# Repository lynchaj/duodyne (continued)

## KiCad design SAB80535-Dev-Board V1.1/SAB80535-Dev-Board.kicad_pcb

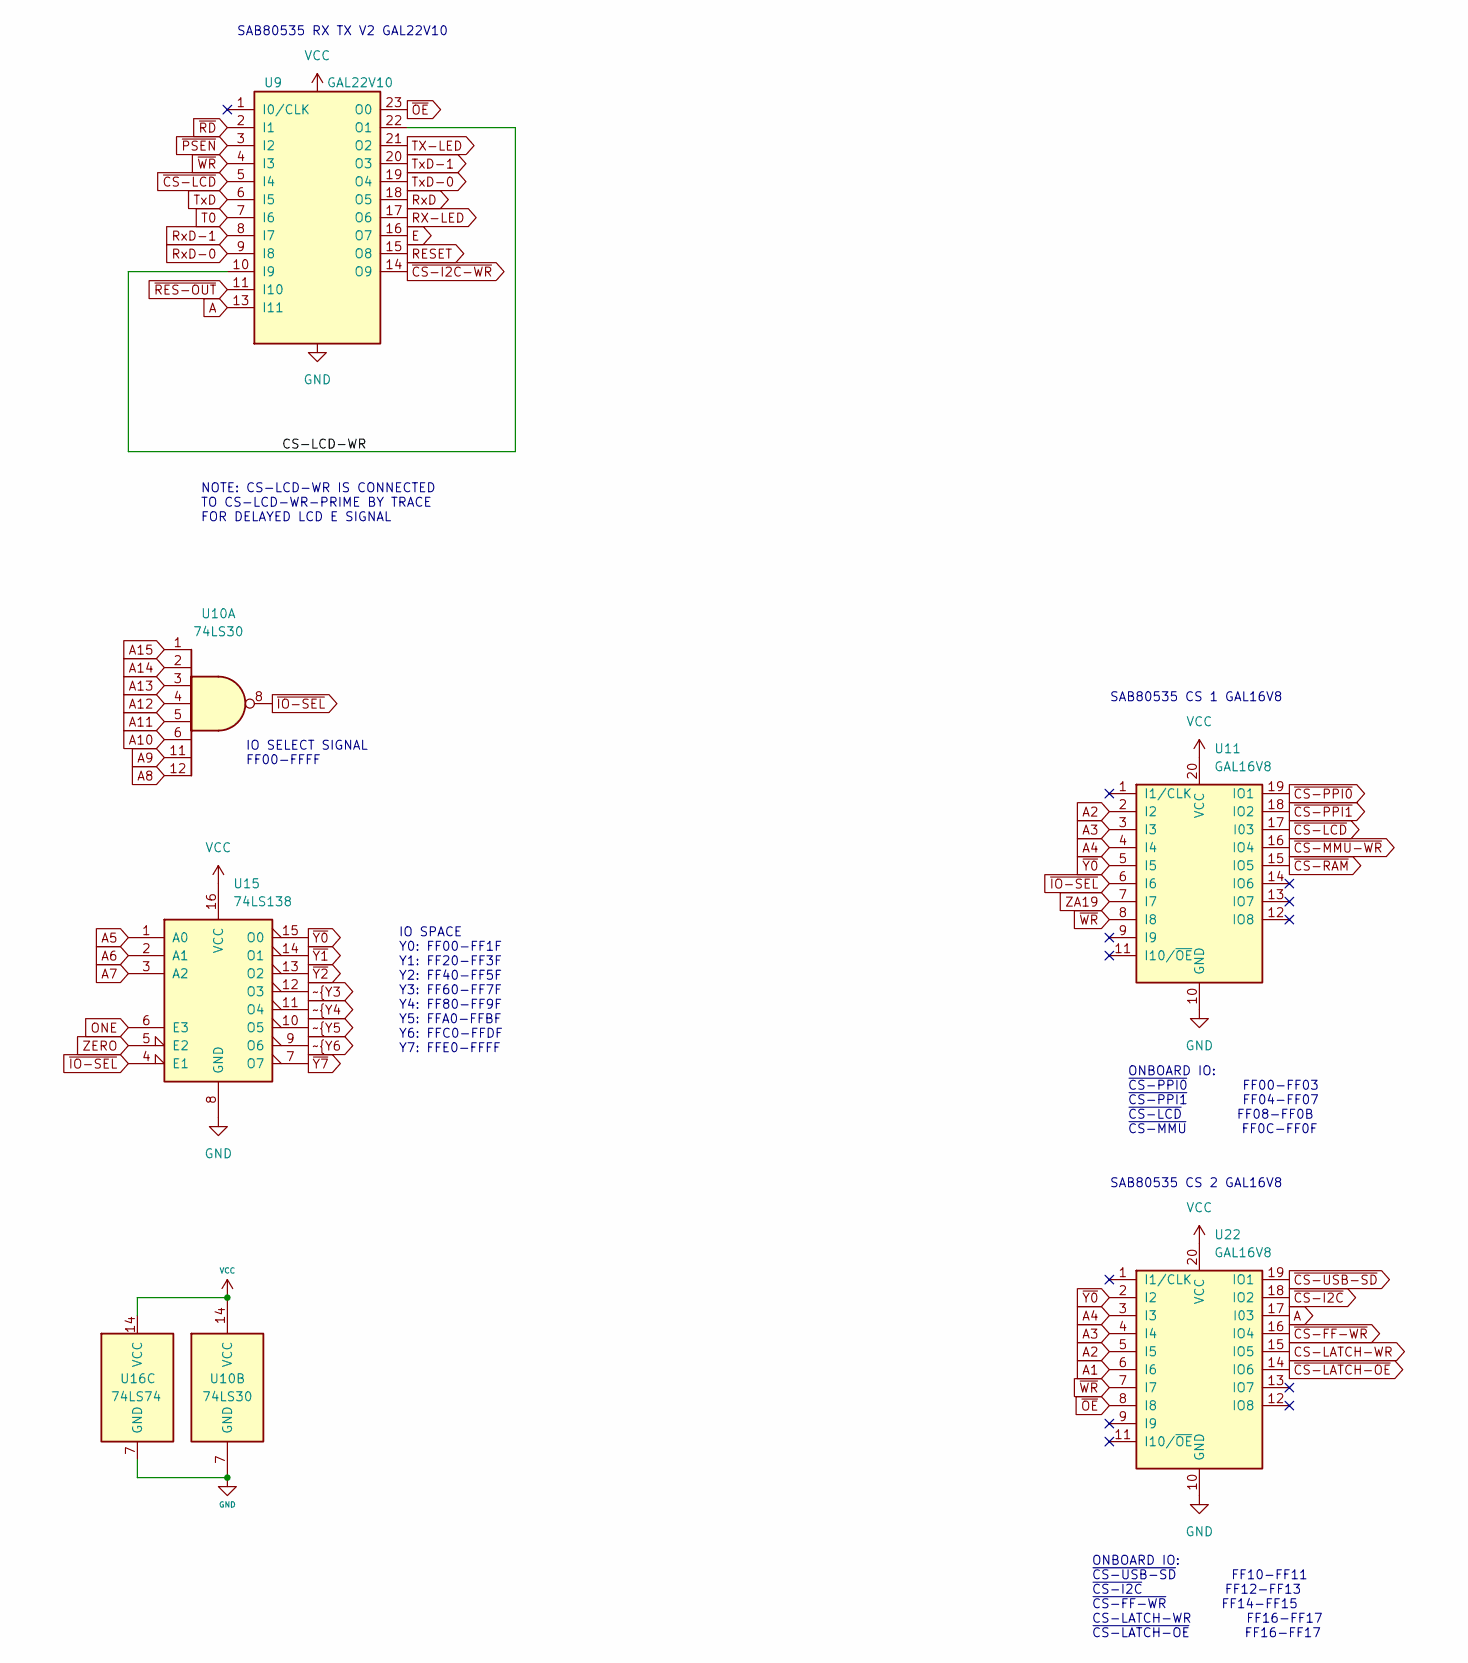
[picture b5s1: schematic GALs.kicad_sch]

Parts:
U9: GAL22V10; DIP-24_W7.62mm_Socket
U10: 74LS30; DIP-14_W7.62mm_Socket
U11, U22: GAL16V8; DIP-20_W7.62mm_Socket
U15: 74LS138; DIP-16_W7.62mm_Socket
U16: 74LS74; DIP-14_W7.62mm_Socket

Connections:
/GALs/CS-LCD-WR: U9.10 (I9), U9.22 (O1)
A: U9.13 (I11), U22.17 (I03)
A1: U22.6 (I6); also elsewhere on the board
A2: U11.2 (I2), U22.5 (I5); also elsewhere on the board
A3: U11.3 (I3), U22.4 (I4); also elsewhere on the board
A4: U11.4 (I4), U22.3 (I3); also elsewhere on the board
A5: U15.1 (A0); also elsewhere on the board
A6: U15.2 (A1); also elsewhere on the board
A7: U15.3 (A2); also elsewhere on the board
A8: U10.12; also elsewhere on the board
A9: U10.11; also elsewhere on the board
A10: U10.6; also elsewhere on the board
A11: U10.5; also elsewhere on the board
A12: U10.4; also elsewhere on the board
A13: U10.3; also elsewhere on the board
A14: U10.2; also elsewhere on the board
A15: U10.1; also elsewhere on the board
CS-LATCH-WR: U22.15 (IO5); also elsewhere on the board
D0: U16.2 (D); also elsewhere on the board
E: U9.16 (O7); also elsewhere on the board
GND: U9.12 (GND), U10.7 (GND), U11.10 (GND), U15.8 (GND), U16.7 (GND), U22.10 (GND); also elsewhere on the board
ONE: U15.6 (E3), U16.4 (~S); also elsewhere on the board
RESET: U9.15 (O8); also elsewhere on the board
RX-LED: U9.17 (O6); also elsewhere on the board
RxD: U9.18 (O5); also elsewhere on the board
RxD-0: U9.9 (I8); also elsewhere on the board
RxD-1: U9.8 (I7); also elsewhere on the board
T0: U9.7 (I6); also elsewhere on the board
TX-LED: U9.21 (O2); also elsewhere on the board
TxD: U9.6 (I5); also elsewhere on the board
TxD-0: U9.19 (O4); also elsewhere on the board
TxD-1: U9.20 (O3); also elsewhere on the board
VCC: U9.24 (VCC), U10.14 (VCC), U11.20 (VCC), U15.16 (VCC), U16.14 (VCC), U22.20 (VCC); also elsewhere on the board
ZA19: U11.7 (I7); also elsewhere on the board
ZERO: U15.5 (E2); also elsewhere on the board
~CS-FF-WR: U16.3 (C), U22.16 (IO4); also elsewhere on the board
~CS-I2C-WR: U9.14 (O9); also elsewhere on the board
~CS-I2C: U22.18 (IO2); also elsewhere on the board
~CS-LATCH-OE: U22.14 (IO6); also elsewhere on the board
~CS-LCD: U9.5 (I4), U11.17 (I03); also elsewhere on the board
~CS-MMU-WR: U11.16 (IO4); also elsewhere on the board
~CS-PPI0: U11.19 (IO1); also elsewhere on the board
~CS-PPI1: U11.18 (IO2); also elsewhere on the board
~CS-RAM: U11.15 (IO5); also elsewhere on the board
~CS-ROM: U11.14 (IO6); also elsewhere on the board
~CS-USB-SD: U22.19 (IO1); also elsewhere on the board
~IO-SEL: U10.8, U11.6 (I6), U15.4 (E1); also elsewhere on the board
~OE: U9.23 (O0), U22.8 (I8); also elsewhere on the board
~PAGE-EN: U16.6 (~Q); also elsewhere on the board
~PSEN: U9.3 (I2); also elsewhere on the board
~RD: U9.2 (I1); also elsewhere on the board
~RES-OUT: U9.11 (I10), U16.1 (~R); also elsewhere on the board
~WR: U9.4 (I3), U11.8 (I8), U22.7 (I7); also elsewhere on the board
~Y0: U11.5 (I5), U15.15 (O0), U22.2 (I2)
~Y1: U15.14 (O1); also elsewhere on the board
~Y2: U15.13 (O2); also elsewhere on the board
~Y7: U15.7 (O7); also elsewhere on the board

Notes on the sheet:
NOTE: CS-LCD-WR IS CONNECTED TO CS-LCD-WR-PRIME BY TRACE FOR DELAYED LCD E SIGNAL
SAB80535 RX TX V2 GAL22V10
IO SELECT SIGNAL FF00-FFFF
SAB80535 CS 2 GAL16V8
IO SPACE Y0: FF00-FF1F Y1: FF20-FF3F Y2: FF40-FF5F Y3: FF60-FF7F Y4: FF80-FF9F Y5: FFA0-FFBF Y6: FFC0-FFDF Y7: FFE0-FFFF
ONBOARD IO: ~{CS-USB-SD} FF10-FF11 ~{CS-I2C} FF12-FF13 ~{CS-FF-WR} FF14-FF15 CS-LATCH-WR FF16-FF17 ~{CS-LATCH-OE} FF16-FF17
SAB80535 CS 1 GAL16V8
ONBOARD IO: ~{CS-PPI0} FF00-FF03 ~{CS-PPI1} FF04-FF07 ~{CS-LCD} FF08-FF0B ~{CS-MMU} FF0C-FF0F

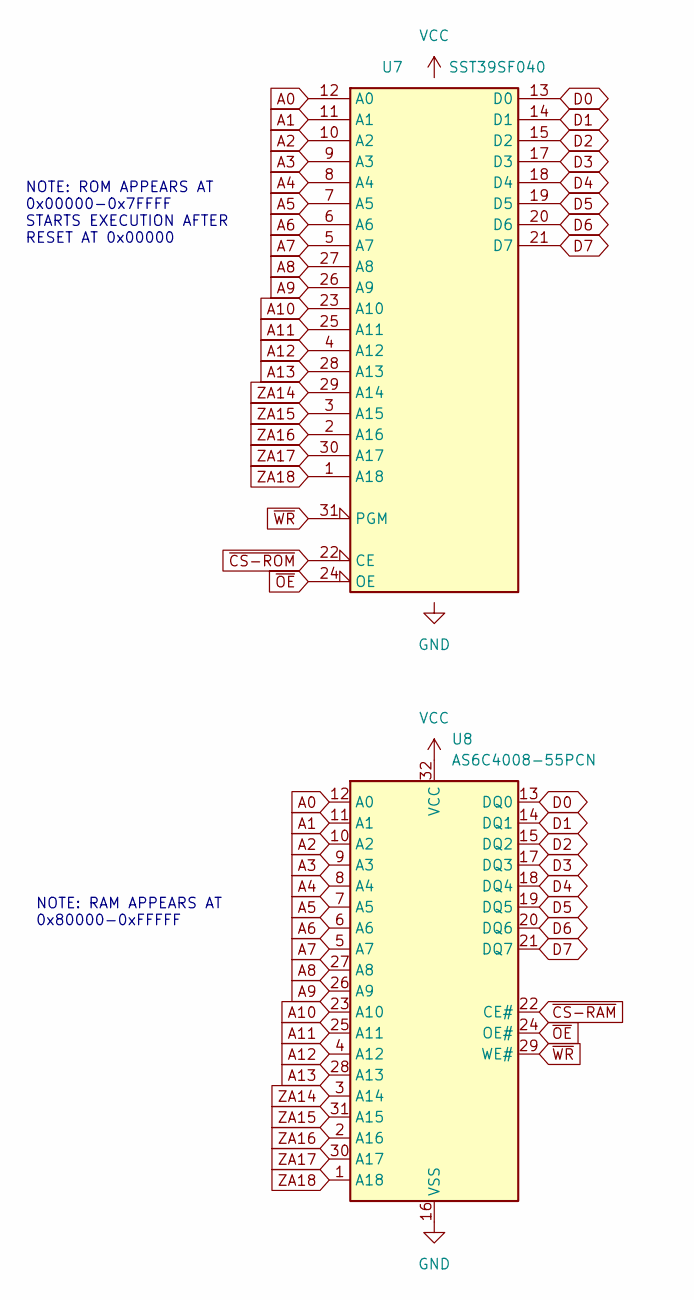
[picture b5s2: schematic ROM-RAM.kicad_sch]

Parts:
U7: SST39SF040; DIP_Socket-32_W11.9_W12.7_W15.24_W17.78_W18.5_3M_232-1285-0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
U8: AS6C4008-55PCN; DIP-32_W15.24mm_Socket

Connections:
A0: U7.12 (A0), U8.12 (A0); also elsewhere on the board
A1: U7.11 (A1), U8.11 (A1); also elsewhere on the board
A2: U7.10 (A2), U8.10 (A2); also elsewhere on the board
A3: U7.9 (A3), U8.9 (A3); also elsewhere on the board
A4: U7.8 (A4), U8.8 (A4); also elsewhere on the board
A5: U7.7 (A5), U8.7 (A5); also elsewhere on the board
A6: U7.6 (A6), U8.6 (A6); also elsewhere on the board
A7: U7.5 (A7), U8.5 (A7); also elsewhere on the board
A8: U7.27 (A8), U8.27 (A8); also elsewhere on the board
A9: U7.26 (A9), U8.26 (A9); also elsewhere on the board
A10: U7.23 (A10), U8.23 (A10); also elsewhere on the board
A11: U7.25 (A11), U8.25 (A11); also elsewhere on the board
A12: U7.4 (A12), U8.4 (A12); also elsewhere on the board
A13: U7.28 (A13), U8.28 (A13); also elsewhere on the board
D0: U7.13 (D0), U8.13 (DQ0); also elsewhere on the board
D1: U7.14 (D1), U8.14 (DQ1); also elsewhere on the board
D2: U7.15 (D2), U8.15 (DQ2); also elsewhere on the board
D3: U7.17 (D3), U8.17 (DQ3); also elsewhere on the board
D4: U7.18 (D4), U8.18 (DQ4); also elsewhere on the board
D5: U7.19 (D5), U8.19 (DQ5); also elsewhere on the board
D6: U7.20 (D6), U8.20 (DQ6); also elsewhere on the board
D7: U7.21 (D7), U8.21 (DQ7); also elsewhere on the board
GND: U7.16 (GND), U8.16 (VSS); also elsewhere on the board
VCC: U7.32 (VCC), U8.32 (VCC); also elsewhere on the board
ZA14: U7.29 (A14), U8.3 (A14); also elsewhere on the board
ZA15: U7.3 (A15), U8.31 (A15); also elsewhere on the board
ZA16: U7.2 (A16), U8.2 (A16); also elsewhere on the board
ZA17: U7.30 (A17), U8.30 (A17); also elsewhere on the board
ZA18: U7.1 (A18), U8.1 (A18); also elsewhere on the board
~CS-RAM: U8.22 (CE#); also elsewhere on the board
~CS-ROM: U7.22 (CE); also elsewhere on the board
~OE: U7.24 (OE), U8.24 (OE#); also elsewhere on the board
~WR: U7.31 (PGM), U8.29 (WE#); also elsewhere on the board

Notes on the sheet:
NOTE: ROM APPEARS AT 0x00000-0x7FFFF STARTS EXECUTION AFTER RESET AT 0x00000
NOTE: RAM APPEARS AT 0x80000-0xFFFFF

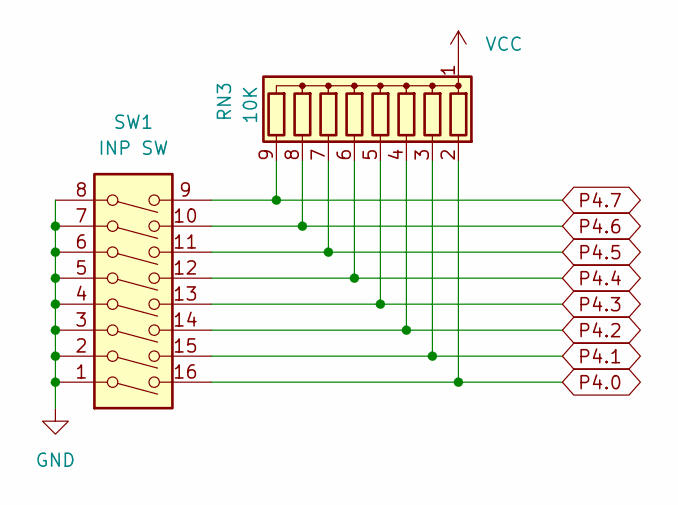
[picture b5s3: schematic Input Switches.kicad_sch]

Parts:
RN3: 10K; R_Array_SIP9
SW1: INP SW; SW_DIP_SPSTx08_Slide_9.78x22.5mm_W7.62mm_P2.54mm

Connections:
GND: SW1.1, SW1.2, SW1.3, SW1.4, SW1.5, SW1.6, SW1.7, SW1.8; also elsewhere on the board
P4.0: RN3.2 (R1), SW1.16; also elsewhere on the board
P4.1: RN3.3 (R2), SW1.15; also elsewhere on the board
P4.2: RN3.4 (R3), SW1.14; also elsewhere on the board
P4.3: RN3.5 (R4), SW1.13; also elsewhere on the board
P4.4: RN3.6 (R5), SW1.12; also elsewhere on the board
P4.5: RN3.7 (R6), SW1.11; also elsewhere on the board
P4.6: RN3.8 (R7), SW1.10; also elsewhere on the board
P4.7: RN3.9 (R8), SW1.9; also elsewhere on the board
VCC: RN3.1 (common); also elsewhere on the board

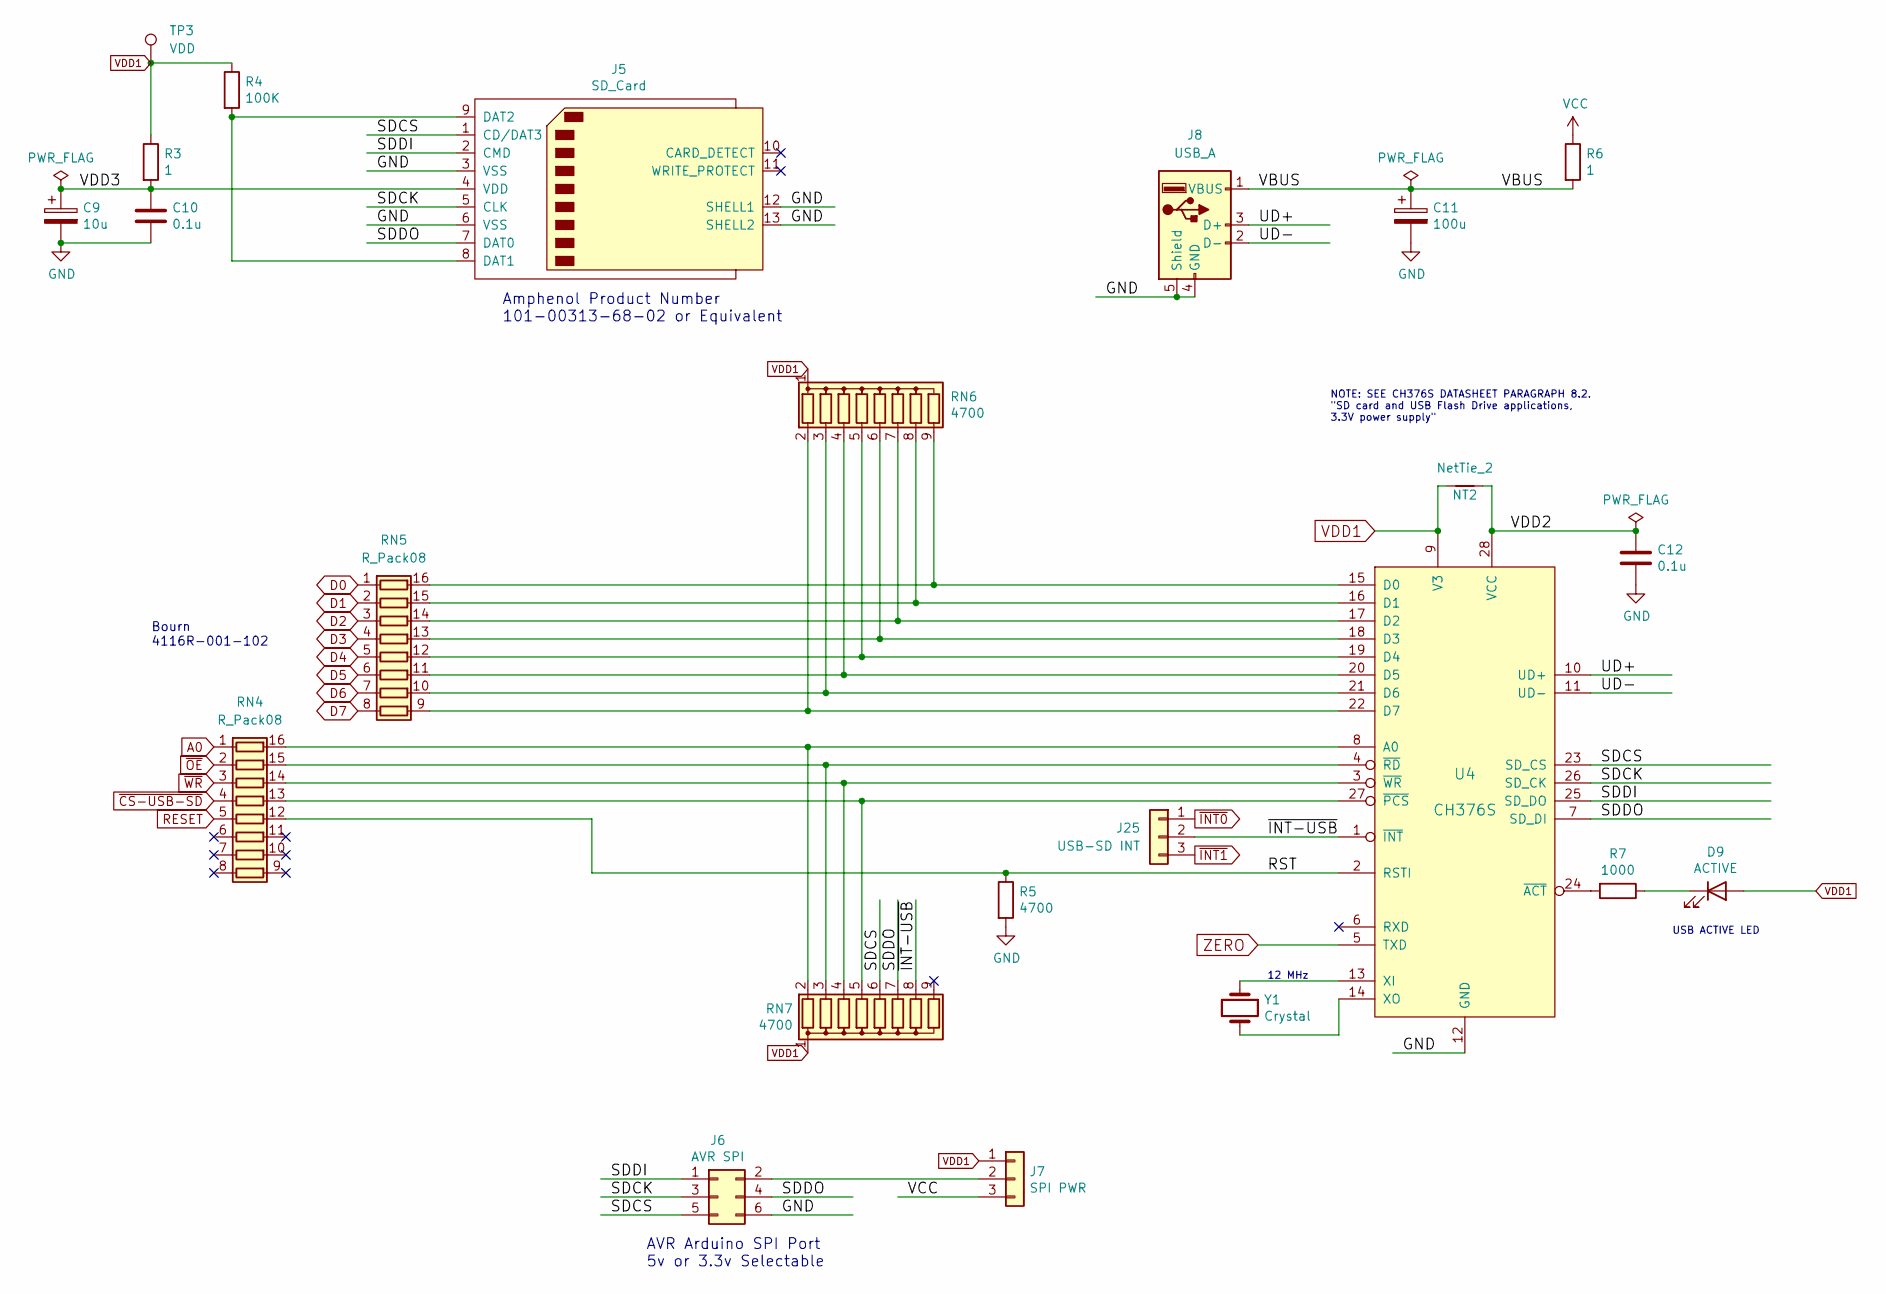
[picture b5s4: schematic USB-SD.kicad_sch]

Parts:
C9: 10u; CP_Radial_D5.0mm_P2.50mm
C10, C12: 0.1u; C_Disc_D5.0mm_W2.5mm_P5.00mm
C11: 100u; CP_Radial_D6.3mm_P2.50mm
D9: ACTIVE; LED_D3.0mm
J5: SD_Card; SD_Card_Receptacle
J6: AVR SPI; PinHeader_2x03_P2.54mm_Vertical
J7: SPI PWR; PinHeader_1x03_P2.54mm_Vertical
J8: USB_A; USB_A_Molex_67643_Horizontal
J25: USB-SD INT; PinHeader_1x03_P2.54mm_Vertical
NT2: NetTie_2; NetTie-2_THT_Pad0.3mm
R3, R6: 1; R_Axial_DIN0207_L6.3mm_D2.5mm_P7.62mm_Horizontal
R4: 100K; R_Axial_DIN0207_L6.3mm_D2.5mm_P7.62mm_Horizontal
R5: 4700; R_Axial_DIN0207_L6.3mm_D2.5mm_P7.62mm_Horizontal
R7: 1000; R_Axial_DIN0207_L6.3mm_D2.5mm_P7.62mm_Horizontal
RN4, RN5: R_Pack08; DIP-16_W7.62mm_Socket
RN6, RN7: 4700; R_Array_SIP9
TP3: VDD; PinHeader_1x01_P2.54mm_Vertical
U4: CH376S; DIP-28_W15.24mm_Socket
Y1: Crystal; Crystal_HC49-4H_Vertical

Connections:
/USB-SD/RST: R5.1, RN4.12 (R5.2), U4.2 (RSTI)
/USB-SD/SDCK: J5.5 (CLK), J6.3, U4.26 (SD_CK)
/USB-SD/SDCS: J5.1 (CD/DAT3), J6.5, RN7.6 (R5), U4.23 (SD_CS)
/USB-SD/SDDI: J5.2 (CMD), J6.1, U4.25 (SD_DO)
/USB-SD/SDDO: J5.7 (DAT0), J6.4, RN7.7 (R6), U4.7 (SD_DI)
/USB-SD/UD+: J8.3 (D+), U4.10 (UD+)
/USB-SD/UD-: J8.2 (D-), U4.11 (UD-)
/USB-SD/VBUS: C11.1, J8.1 (VBUS), R6.2
/USB-SD/VDD2: C12.1, NT2.1, U4.28 (VCC)
/USB-SD/VDD3: C9.1, C10.1, J5.4 (VDD), R3.2
/USB-SD/~INT-USB: J25.2, RN7.8 (R7), U4.1 (~INT)
A0: RN4.1 (R1.1); also elsewhere on the board
D0: RN5.1 (R1.1); also elsewhere on the board
D1: RN5.2 (R2.1); also elsewhere on the board
D2: RN5.3 (R3.1); also elsewhere on the board
D3: RN5.4 (R4.1); also elsewhere on the board
D4: RN5.5 (R5.1); also elsewhere on the board
D5: RN5.6 (R6.1); also elsewhere on the board
D6: RN5.7 (R7.1); also elsewhere on the board
D7: RN5.8 (R8.1); also elsewhere on the board
GND: C9.2, C10.2, C11.2, C12.2, J5.3 (VSS), J5.6 (VSS), J5.12 (SHELL1), J5.13 (SHELL2), J6.6, J8.4 (GND), J8.5 (Shield), R5.2, U4.12 (GND); also elsewhere on the board
unnamed: D9.1 (K), R7.1
unnamed: J5.8 (DAT1), J5.9 (DAT2), R4.2
unnamed: J6.2, J7.2
unnamed: R7.2, U4.24 (~ACT)
unnamed: RN4.13 (R4.2), RN7.5 (R4), U4.27 (~PCS)
unnamed: RN4.14 (R3.2), RN7.4 (R3), U4.3 (~WR)
unnamed: RN4.15 (R2.2), RN7.3 (R2), U4.4 (~RD)
unnamed: RN4.16 (R1.2), RN7.2 (R1), U4.8 (A0)
unnamed: RN5.9 (R8.2), RN6.2 (R1), U4.22 (D7)
unnamed: RN5.10 (R7.2), RN6.3 (R2), U4.21 (D6)
unnamed: RN5.11 (R6.2), RN6.4 (R3), U4.20 (D5)
unnamed: RN5.12 (R5.2), RN6.5 (R4), U4.19 (D4)
unnamed: RN5.13 (R4.2), RN6.6 (R5), U4.18 (D3)
unnamed: RN5.14 (R3.2), RN6.7 (R6), U4.17 (D2)
unnamed: RN5.15 (R2.2), RN6.8 (R7), U4.16 (D1)
unnamed: RN5.16 (R1.2), RN6.9 (R8), U4.15 (D0)
unnamed: U4.13 (XI), Y1.1
unnamed: U4.14 (XO), Y1.2
RESET: RN4.5 (R5.1); also elsewhere on the board
VCC: J7.3, R6.1; also elsewhere on the board
VDD1: D9.2 (A), J7.1, NT2.2, R3.1, R4.1, RN6.1 (common), RN7.1 (common), TP3.1, U4.9 (V3); also elsewhere on the board
ZERO: U4.5 (TXD); also elsewhere on the board
~CS-USB-SD: RN4.4 (R4.1); also elsewhere on the board
~INT0: J25.1; also elsewhere on the board
~INT1: J25.3; also elsewhere on the board
~OE: RN4.2 (R2.1); also elsewhere on the board
~WR: RN4.3 (R3.1); also elsewhere on the board

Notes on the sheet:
12 MHz
Amphenol Product Number 101-00313-68-02 or Equivalent
AVR Arduino SPI Port 5v or 3.3v Selectable
USB ACTIVE LED
Bourn 4116R-001-102
NOTE: SEE CH376S DATASHEET PARAGRAPH 8.2. "SD card and USB Flash Drive applications, 3.3V power supply"

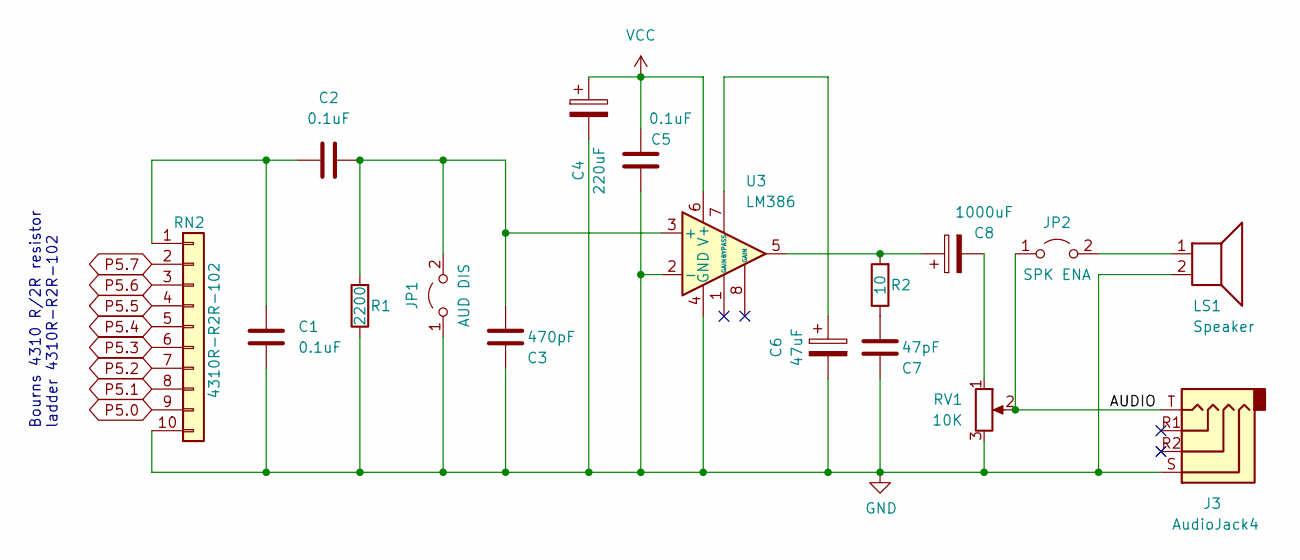
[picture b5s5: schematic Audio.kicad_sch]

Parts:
C1, C2, C5: 0.1uF; C_Disc_D5.0mm_W2.5mm_P5.00mm
C3: 470pF; C_Disc_D3.8mm_W2.6mm_P2.50mm
C4: 220uF; CP_Radial_D8.0mm_P2.50mm
C6: 47uF; CP_Radial_D5.0mm_P2.50mm
C7: 47pF; C_Disc_D3.8mm_W2.6mm_P2.50mm
C8: 1000uF; CP_Radial_D8.0mm_P2.50mm
J3: AudioJack4; Jack_3.5mm_PJ320E_Horizontal
JP1: AUD DIS; PinHeader_1x02_P2.54mm_Vertical
JP2: SPK ENA; PinHeader_1x02_P2.54mm_Vertical
LS1: Speaker; Jameco PCB Speaker 30mm 135722
R1: 2200; R_Axial_DIN0207_L6.3mm_D2.5mm_P7.62mm_Horizontal
R2: 10; R_Axial_DIN0207_L6.3mm_D2.5mm_P7.62mm_Horizontal
RN2: 4310R-R2R-102; R_Array_SIP10
RV1: 10K; Potentiometer_Bourns_3386P_Vertical
U3: LM386; DIP-8_W7.62mm_Socket

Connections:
/Audio/AUDIO: J3.T, JP2.1 (A), RV1.2
GND: C1.2, C3.2, C4.2, C5.1, C6.2, C7.2, J3.S, JP1.1 (A), LS1.2, R1.1, RN2.10, RV1.3, U3.2 (-), U3.4 (GND); also elsewhere on the board
unnamed: C1.1, C2.1, RN2.1
unnamed: C2.2, C3.1, JP1.2 (B), R1.2, U3.3 (+)
unnamed: C6.1, U3.7 (BYPASS)
unnamed: C7.1, R2.1
unnamed: C8.1, R2.2, U3.5
unnamed: C8.2, RV1.1
unnamed: JP2.2 (B), LS1.1
P5.0: RN2.9; also elsewhere on the board
P5.1: RN2.8; also elsewhere on the board
P5.2: RN2.7; also elsewhere on the board
P5.3: RN2.6; also elsewhere on the board
P5.4: RN2.5; also elsewhere on the board
P5.5: RN2.4; also elsewhere on the board
P5.6: RN2.3; also elsewhere on the board
P5.7: RN2.2; also elsewhere on the board
VCC: C4.1, C5.2, U3.6 (V+); also elsewhere on the board

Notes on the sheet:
Bourns 4310 R/2R resistor ladder 4310R-R2R-102

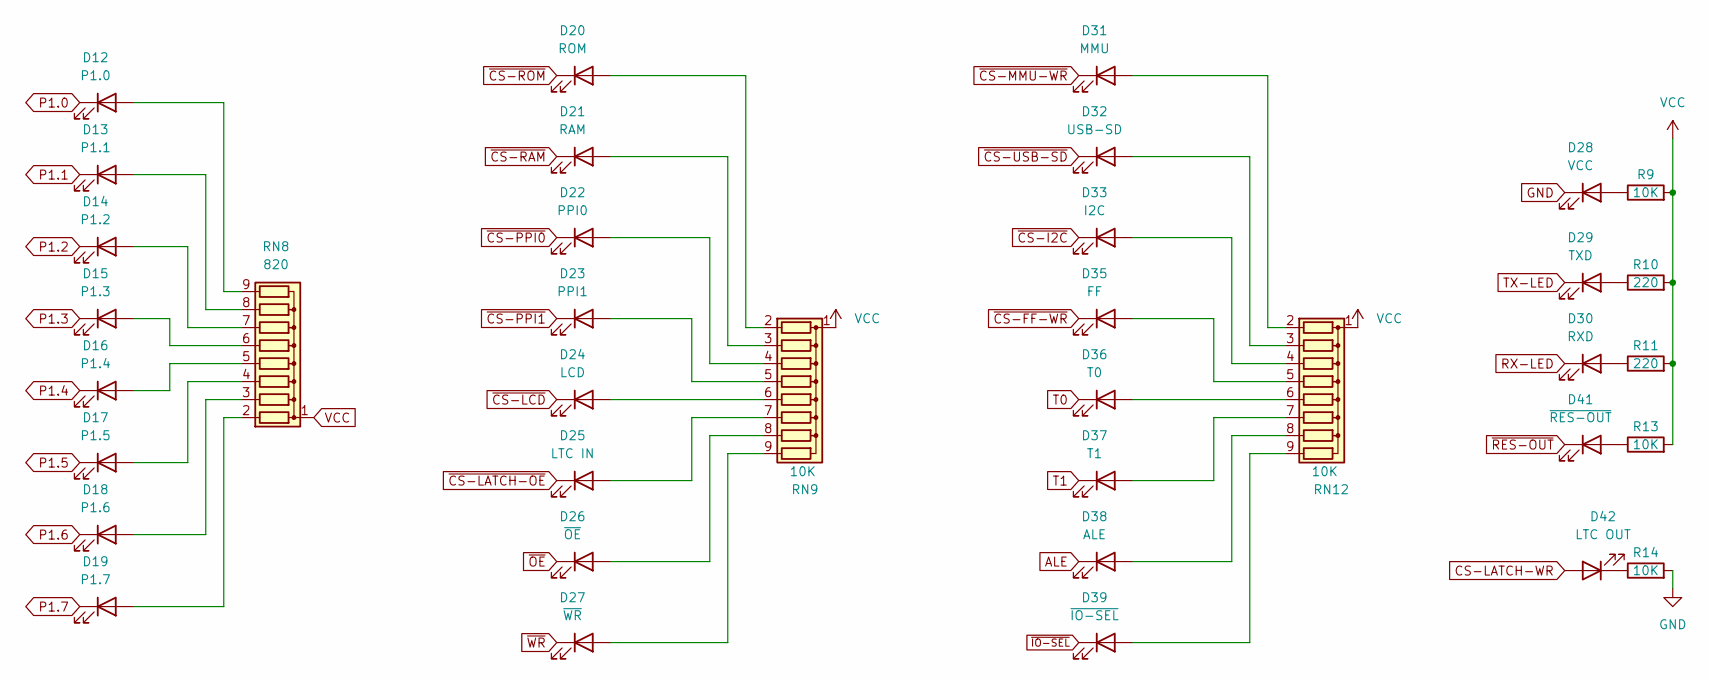
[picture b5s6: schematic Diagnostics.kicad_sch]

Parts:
D12: P1.0; LED_D3.0mm
D13: P1.1; LED_D3.0mm
D14: P1.2; LED_D3.0mm
D15: P1.3; LED_D3.0mm
D16: P1.4; LED_D3.0mm
D17: P1.5; LED_D3.0mm
D18: P1.6; LED_D3.0mm
D19: P1.7; LED_D3.0mm
D20: ROM; LED_D3.0mm
D21: RAM; LED_D3.0mm
D22: PPI0; LED_D3.0mm
D23: PPI1; LED_D3.0mm
D24: LCD; LED_D3.0mm
D25: LTC IN; LED_D3.0mm
D26: ~{OE}; LED_D3.0mm
D27: ~{WR}; LED_D3.0mm
D28: VCC; LED_D3.0mm
D29: TXD; LED_D3.0mm
D30: RXD; LED_D3.0mm
D31: MMU; LED_D3.0mm
D32: USB-SD; LED_D3.0mm
D33: I2C; LED_D3.0mm
D35: FF; LED_D3.0mm
D36: T0; LED_D3.0mm
D37: T1; LED_D3.0mm
D38: ALE; LED_D3.0mm
D39: ~{IO-SEL}; LED_D3.0mm
D41: ~{RES-OUT}; LED_D3.0mm
D42: LTC OUT; LED_D3.0mm
R9, R13, R14: 10K; R_Axial_DIN0207_L6.3mm_D2.5mm_P7.62mm_Horizontal
R10, R11: 220; R_Axial_DIN0207_L6.3mm_D2.5mm_P7.62mm_Horizontal
RN8: 820; R_Array_SIP9
RN9, RN12: 10K; R_Array_SIP9

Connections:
ALE: D38.1 (K); also elsewhere on the board
CS-LATCH-WR: D42.2 (A); also elsewhere on the board
GND: D28.1 (K), R14.2; also elsewhere on the board
unnamed: D12.2 (A), RN8.9 (R8)
unnamed: D13.2 (A), RN8.8 (R7)
unnamed: D14.2 (A), RN8.7 (R6)
unnamed: D15.2 (A), RN8.6 (R5)
unnamed: D16.2 (A), RN8.5 (R4)
unnamed: D17.2 (A), RN8.4 (R3)
unnamed: D18.2 (A), RN8.3 (R2)
unnamed: D19.2 (A), RN8.2 (R1)
unnamed: D20.2 (A), RN9.2 (R1)
unnamed: D21.2 (A), RN9.3 (R2)
unnamed: D22.2 (A), RN9.4 (R3)
unnamed: D23.2 (A), RN9.5 (R4)
unnamed: D24.2 (A), RN9.6 (R5)
unnamed: D25.2 (A), RN9.7 (R6)
unnamed: D26.2 (A), RN9.8 (R7)
unnamed: D27.2 (A), RN9.9 (R8)
unnamed: D28.2 (A), R9.1
unnamed: D29.2 (A), R10.1
unnamed: D30.2 (A), R11.1
unnamed: D31.2 (A), RN12.2 (R1)
unnamed: D32.2 (A), RN12.3 (R2)
unnamed: D33.2 (A), RN12.4 (R3)
unnamed: D35.2 (A), RN12.5 (R4)
unnamed: D36.2 (A), RN12.6 (R5)
unnamed: D37.2 (A), RN12.7 (R6)
unnamed: D38.2 (A), RN12.8 (R7)
unnamed: D39.2 (A), RN12.9 (R8)
unnamed: D41.2 (A), R13.1
unnamed: D42.1 (K), R14.1
P1.0: D12.1 (K); also elsewhere on the board
P1.1: D13.1 (K); also elsewhere on the board
P1.2: D14.1 (K); also elsewhere on the board
P1.3: D15.1 (K); also elsewhere on the board
P1.4: D16.1 (K); also elsewhere on the board
P1.5: D17.1 (K); also elsewhere on the board
P1.6: D18.1 (K); also elsewhere on the board
P1.7: D19.1 (K); also elsewhere on the board
RX-LED: D30.1 (K); also elsewhere on the board
T0: D36.1 (K); also elsewhere on the board
T1: D37.1 (K); also elsewhere on the board
TX-LED: D29.1 (K); also elsewhere on the board
VCC: R9.2, R10.2, R11.2, R13.2, RN8.1 (common), RN9.1 (common), RN12.1 (common); also elsewhere on the board
~CS-FF-WR: D35.1 (K); also elsewhere on the board
~CS-I2C: D33.1 (K); also elsewhere on the board
~CS-LATCH-OE: D25.1 (K); also elsewhere on the board
~CS-LCD: D24.1 (K); also elsewhere on the board
~CS-MMU-WR: D31.1 (K); also elsewhere on the board
~CS-PPI0: D22.1 (K); also elsewhere on the board
~CS-PPI1: D23.1 (K); also elsewhere on the board
~CS-RAM: D21.1 (K); also elsewhere on the board
~CS-ROM: D20.1 (K); also elsewhere on the board
~CS-USB-SD: D32.1 (K); also elsewhere on the board
~IO-SEL: D39.1 (K); also elsewhere on the board
~OE: D26.1 (K); also elsewhere on the board
~RES-OUT: D41.1 (K); also elsewhere on the board
~WR: D27.1 (K); also elsewhere on the board

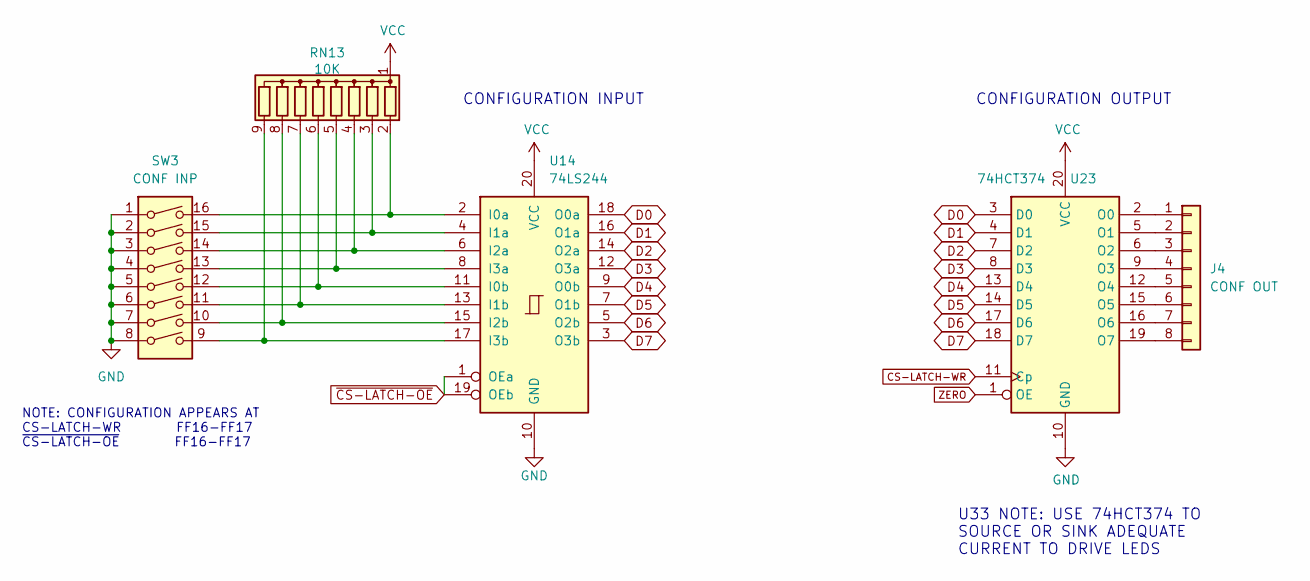
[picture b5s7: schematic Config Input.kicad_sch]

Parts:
J4: CONF OUT; PinHeader_1x08_P2.54mm_Vertical
RN13: 10K; R_Array_SIP9
SW3: CONF INP; SW_DIP_SPSTx08_Slide_9.78x22.5mm_W7.62mm_P2.54mm
U14: 74LS244; DIP-20_W7.62mm_Socket
U23: 74HCT374; DIP-20_W7.62mm_Socket

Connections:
CS-LATCH-WR: U23.11 (Cp); also elsewhere on the board
D0: U14.18 (O0a), U23.3 (D0); also elsewhere on the board
D1: U14.16 (O1a), U23.4 (D1); also elsewhere on the board
D2: U14.14 (O2a), U23.7 (D2); also elsewhere on the board
D3: U14.12 (O3a), U23.8 (D3); also elsewhere on the board
D4: U14.9 (O0b), U23.13 (D4); also elsewhere on the board
D5: U14.7 (O1b), U23.14 (D5); also elsewhere on the board
D6: U14.5 (O2b), U23.17 (D6); also elsewhere on the board
D7: U14.3 (O3b), U23.18 (D7); also elsewhere on the board
GND: SW3.1, SW3.2, SW3.3, SW3.4, SW3.5, SW3.6, SW3.7, SW3.8, U14.10 (GND), U23.10 (GND); also elsewhere on the board
unnamed: J4.1, U23.2 (O0)
unnamed: J4.2, U23.5 (O1)
unnamed: J4.3, U23.6 (O2)
unnamed: J4.4, U23.9 (O3)
unnamed: J4.5, U23.12 (O4)
unnamed: J4.6, U23.15 (O5)
unnamed: J4.7, U23.16 (O6)
unnamed: J4.8, U23.19 (O7)
unnamed: RN13.2 (R1), SW3.16, U14.2 (I0a)
unnamed: RN13.3 (R2), SW3.15, U14.4 (I1a)
unnamed: RN13.4 (R3), SW3.14, U14.6 (I2a)
unnamed: RN13.5 (R4), SW3.13, U14.8 (I3a)
unnamed: RN13.6 (R5), SW3.12, U14.11 (I0b)
unnamed: RN13.7 (R6), SW3.11, U14.13 (I1b)
unnamed: RN13.8 (R7), SW3.10, U14.15 (I2b)
unnamed: RN13.9 (R8), SW3.9, U14.17 (I3b)
VCC: RN13.1 (common), U14.20 (VCC), U23.20 (VCC); also elsewhere on the board
ZERO: U23.1 (OE); also elsewhere on the board
~CS-LATCH-OE: U14.1 (OEa), U14.19 (OEb); also elsewhere on the board

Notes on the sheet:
U33 NOTE: USE 74HCT374 TO SOURCE OR SINK ADEQUATE CURRENT TO DRIVE LEDS
CONFIGURATION INPUT
CONFIGURATION OUTPUT
NOTE: CONFIGURATION APPEARS AT CS-LATCH-WR FF16-FF17 ~{CS-LATCH-OE} FF16-FF17

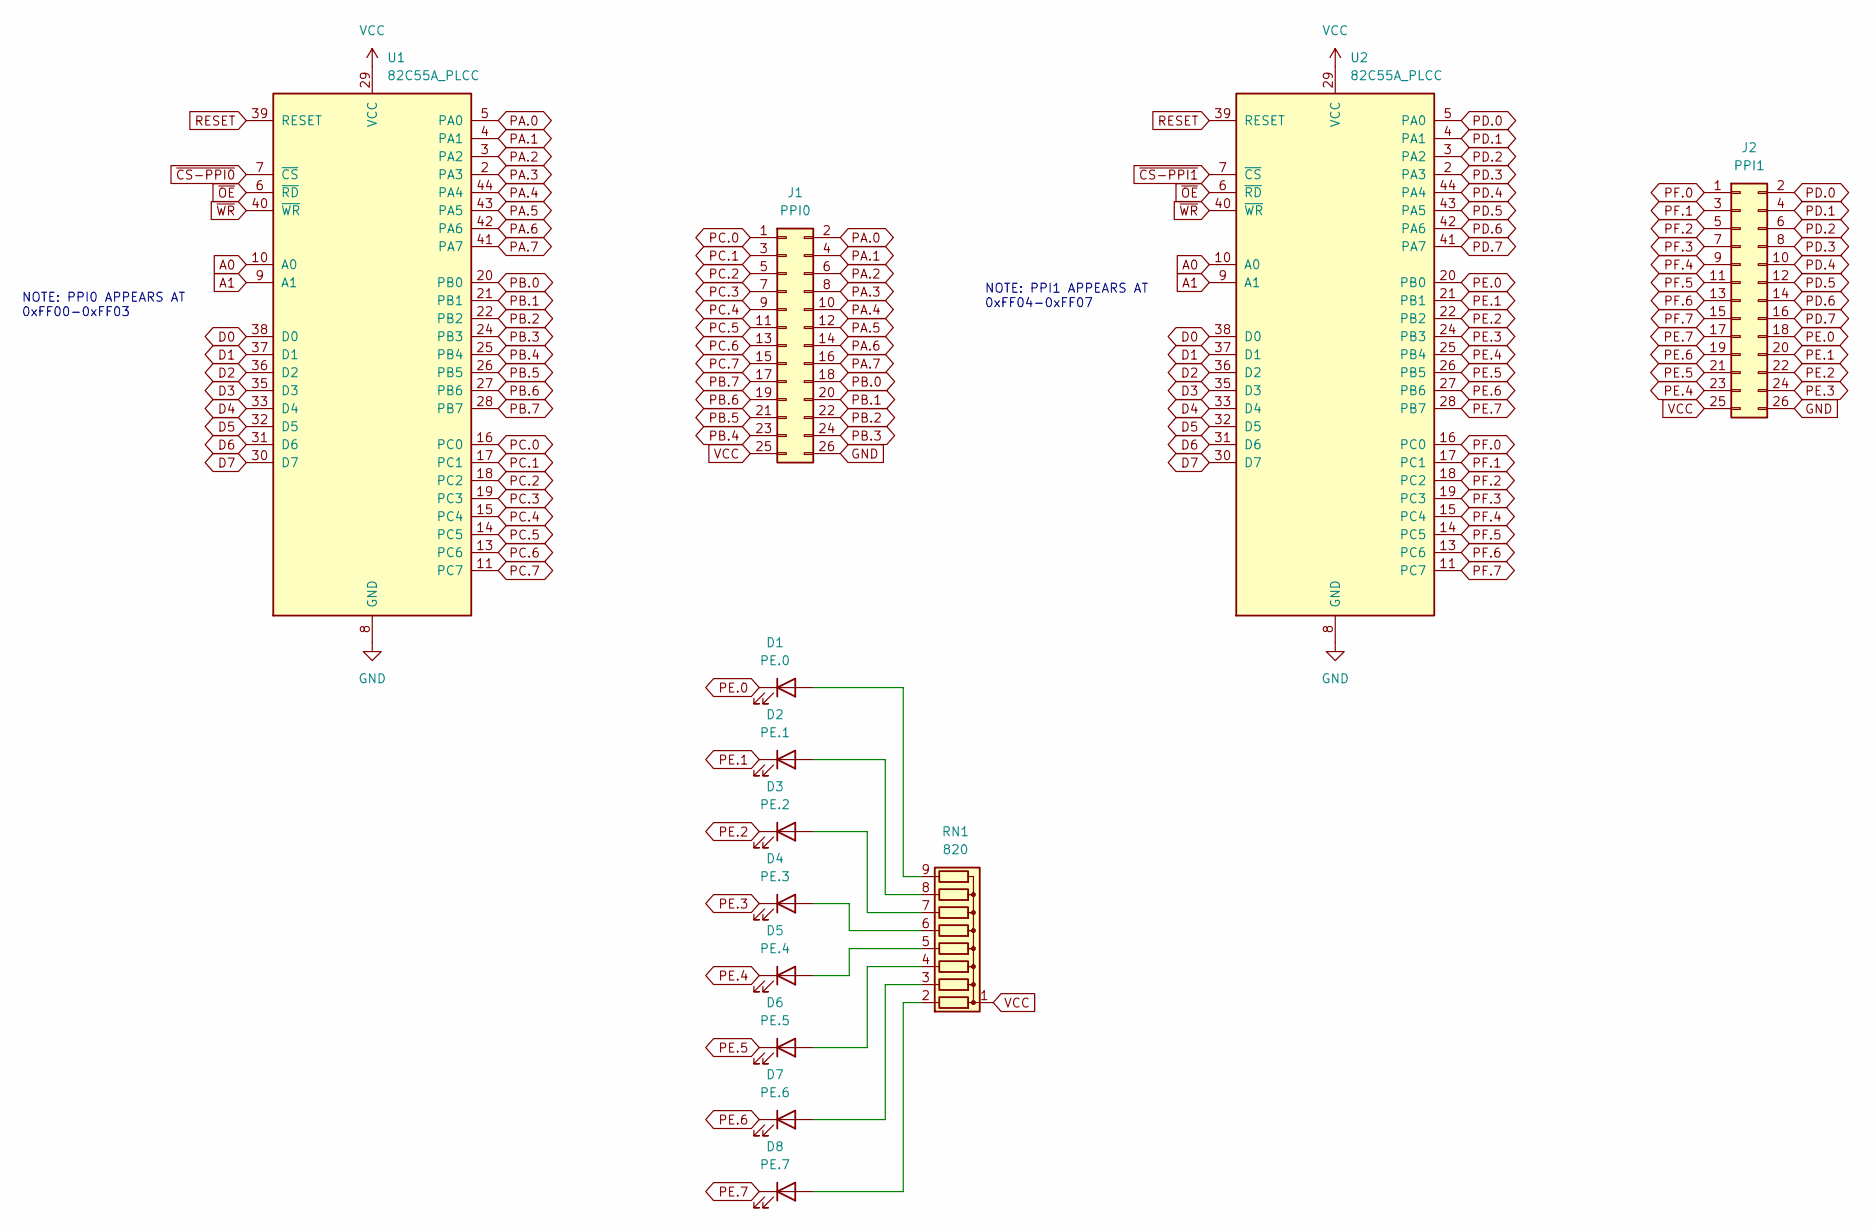
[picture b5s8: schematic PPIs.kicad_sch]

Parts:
D1: PE.0; LED_D3.0mm
D2: PE.1; LED_D3.0mm
D3: PE.2; LED_D3.0mm
D4: PE.3; LED_D3.0mm
D5: PE.4; LED_D3.0mm
D6: PE.5; LED_D3.0mm
D7: PE.6; LED_D3.0mm
D8: PE.7; LED_D3.0mm
J1: PPI0; IDC-Header_2x13_P2.54mm_Horizontal
J2: PPI1; IDC-Header_2x13_P2.54mm_Horizontal
RN1: 820; R_Array_SIP9
U1, U2: 82C55A_PLCC; PLCC-44_THT-Socket

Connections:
A0: U1.10 (A0), U2.10 (A0); also elsewhere on the board
A1: U1.9 (A1), U2.9 (A1); also elsewhere on the board
D0: U1.38 (D0), U2.38 (D0); also elsewhere on the board
D1: U1.37 (D1), U2.37 (D1); also elsewhere on the board
D2: U1.36 (D2), U2.36 (D2); also elsewhere on the board
D3: U1.35 (D3), U2.35 (D3); also elsewhere on the board
D4: U1.33 (D4), U2.33 (D4); also elsewhere on the board
D5: U1.32 (D5), U2.32 (D5); also elsewhere on the board
D6: U1.31 (D6), U2.31 (D6); also elsewhere on the board
D7: U1.30 (D7), U2.30 (D7); also elsewhere on the board
GND: J1.26, J2.26, U1.8 (GND), U2.8 (GND); also elsewhere on the board
unnamed: D1.2 (A), RN1.9 (R8)
unnamed: D2.2 (A), RN1.8 (R7)
unnamed: D3.2 (A), RN1.7 (R6)
unnamed: D4.2 (A), RN1.6 (R5)
unnamed: D5.2 (A), RN1.5 (R4)
unnamed: D6.2 (A), RN1.4 (R3)
unnamed: D7.2 (A), RN1.3 (R2)
unnamed: D8.2 (A), RN1.2 (R1)
PA.0: J1.2, U1.5 (PA0)
PA.1: J1.4, U1.4 (PA1)
PA.2: J1.6, U1.3 (PA2)
PA.3: J1.8, U1.2 (PA3)
PA.4: J1.10, U1.44 (PA4)
PA.5: J1.12, U1.43 (PA5)
PA.6: J1.14, U1.42 (PA6)
PA.7: J1.16, U1.41 (PA7)
PB.0: J1.18, U1.20 (PB0)
PB.1: J1.20, U1.21 (PB1)
PB.2: J1.22, U1.22 (PB2)
PB.3: J1.24, U1.24 (PB3)
PB.4: J1.23, U1.25 (PB4)
PB.5: J1.21, U1.26 (PB5)
PB.6: J1.19, U1.27 (PB6)
PB.7: J1.17, U1.28 (PB7)
PC.0: J1.1, U1.16 (PC0)
PC.1: J1.3, U1.17 (PC1)
PC.2: J1.5, U1.18 (PC2)
PC.3: J1.7, U1.19 (PC3)
PC.4: J1.9, U1.15 (PC4)
PC.5: J1.11, U1.14 (PC5)
PC.6: J1.13, U1.13 (PC6)
PC.7: J1.15, U1.11 (PC7)
PD.0: J2.2, U2.5 (PA0)
PD.1: J2.4, U2.4 (PA1)
PD.2: J2.6, U2.3 (PA2)
PD.3: J2.8, U2.2 (PA3)
PD.4: J2.10, U2.44 (PA4)
PD.5: J2.12, U2.43 (PA5)
PD.6: J2.14, U2.42 (PA6)
PD.7: J2.16, U2.41 (PA7)
PE.0: D1.1 (K), J2.18, U2.20 (PB0)
PE.1: D2.1 (K), J2.20, U2.21 (PB1)
PE.2: D3.1 (K), J2.22, U2.22 (PB2)
PE.3: D4.1 (K), J2.24, U2.24 (PB3)
PE.4: D5.1 (K), J2.23, U2.25 (PB4)
PE.5: D6.1 (K), J2.21, U2.26 (PB5)
PE.6: D7.1 (K), J2.19, U2.27 (PB6)
PE.7: D8.1 (K), J2.17, U2.28 (PB7)
PF.0: J2.1, U2.16 (PC0)
PF.1: J2.3, U2.17 (PC1)
PF.2: J2.5, U2.18 (PC2)
PF.3: J2.7, U2.19 (PC3)
PF.4: J2.9, U2.15 (PC4)
PF.5: J2.11, U2.14 (PC5)
PF.6: J2.13, U2.13 (PC6)
PF.7: J2.15, U2.11 (PC7)
RESET: U1.39 (RESET), U2.39 (RESET); also elsewhere on the board
VCC: J1.25, J2.25, RN1.1 (common), U1.29 (VCC), U2.29 (VCC); also elsewhere on the board
~CS-PPI0: U1.7 (~CS); also elsewhere on the board
~CS-PPI1: U2.7 (~CS); also elsewhere on the board
~OE: U1.6 (~RD), U2.6 (~RD); also elsewhere on the board
~WR: U1.40 (~WR), U2.40 (~WR); also elsewhere on the board

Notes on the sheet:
NOTE: PPI0 APPEARS AT 0xFF00-0xFF03
NOTE: PPI1 APPEARS AT 0xFF04-0xFF07
